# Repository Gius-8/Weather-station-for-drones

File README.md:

## Weather station for drones
The project consists of a kit for drones that includes an electronic device that functions as a meteorological station used for monitoring the values of environmental temperature, of atmospheric pressure and of humidity. The whole device'll work thanks to Arduino/Genuino MKR1000.
The electronic device will have inside a GPS locator so as to know the exact position of the analog readings of the different sensors.
The values acquired will be preserved in a KML files on a microSD and you can view them with Google Earth or Google Maps by simply importing the KML file.
They can be monitored in real time via Wi-Fi hotspot using a Smatphone, Tablet or PC.
In addition to the meteorological data, the device can acquire altitude, geographical coordinates and the speed of the drone in m/s.
The device consumes little power and can be powered by a 3.7V LiPo thanks to the potential of mkr1000 board.
In summary, the device will have the following characteristics:
You will be able to acquire:

- Temperature
- Atmospheric pressure
- Humidity
- Speed
- Altitude drone
- Geographic coordinates

Link tutorial: https://www.hackster.io/gius_8/weather-station-for-drones-1184cd

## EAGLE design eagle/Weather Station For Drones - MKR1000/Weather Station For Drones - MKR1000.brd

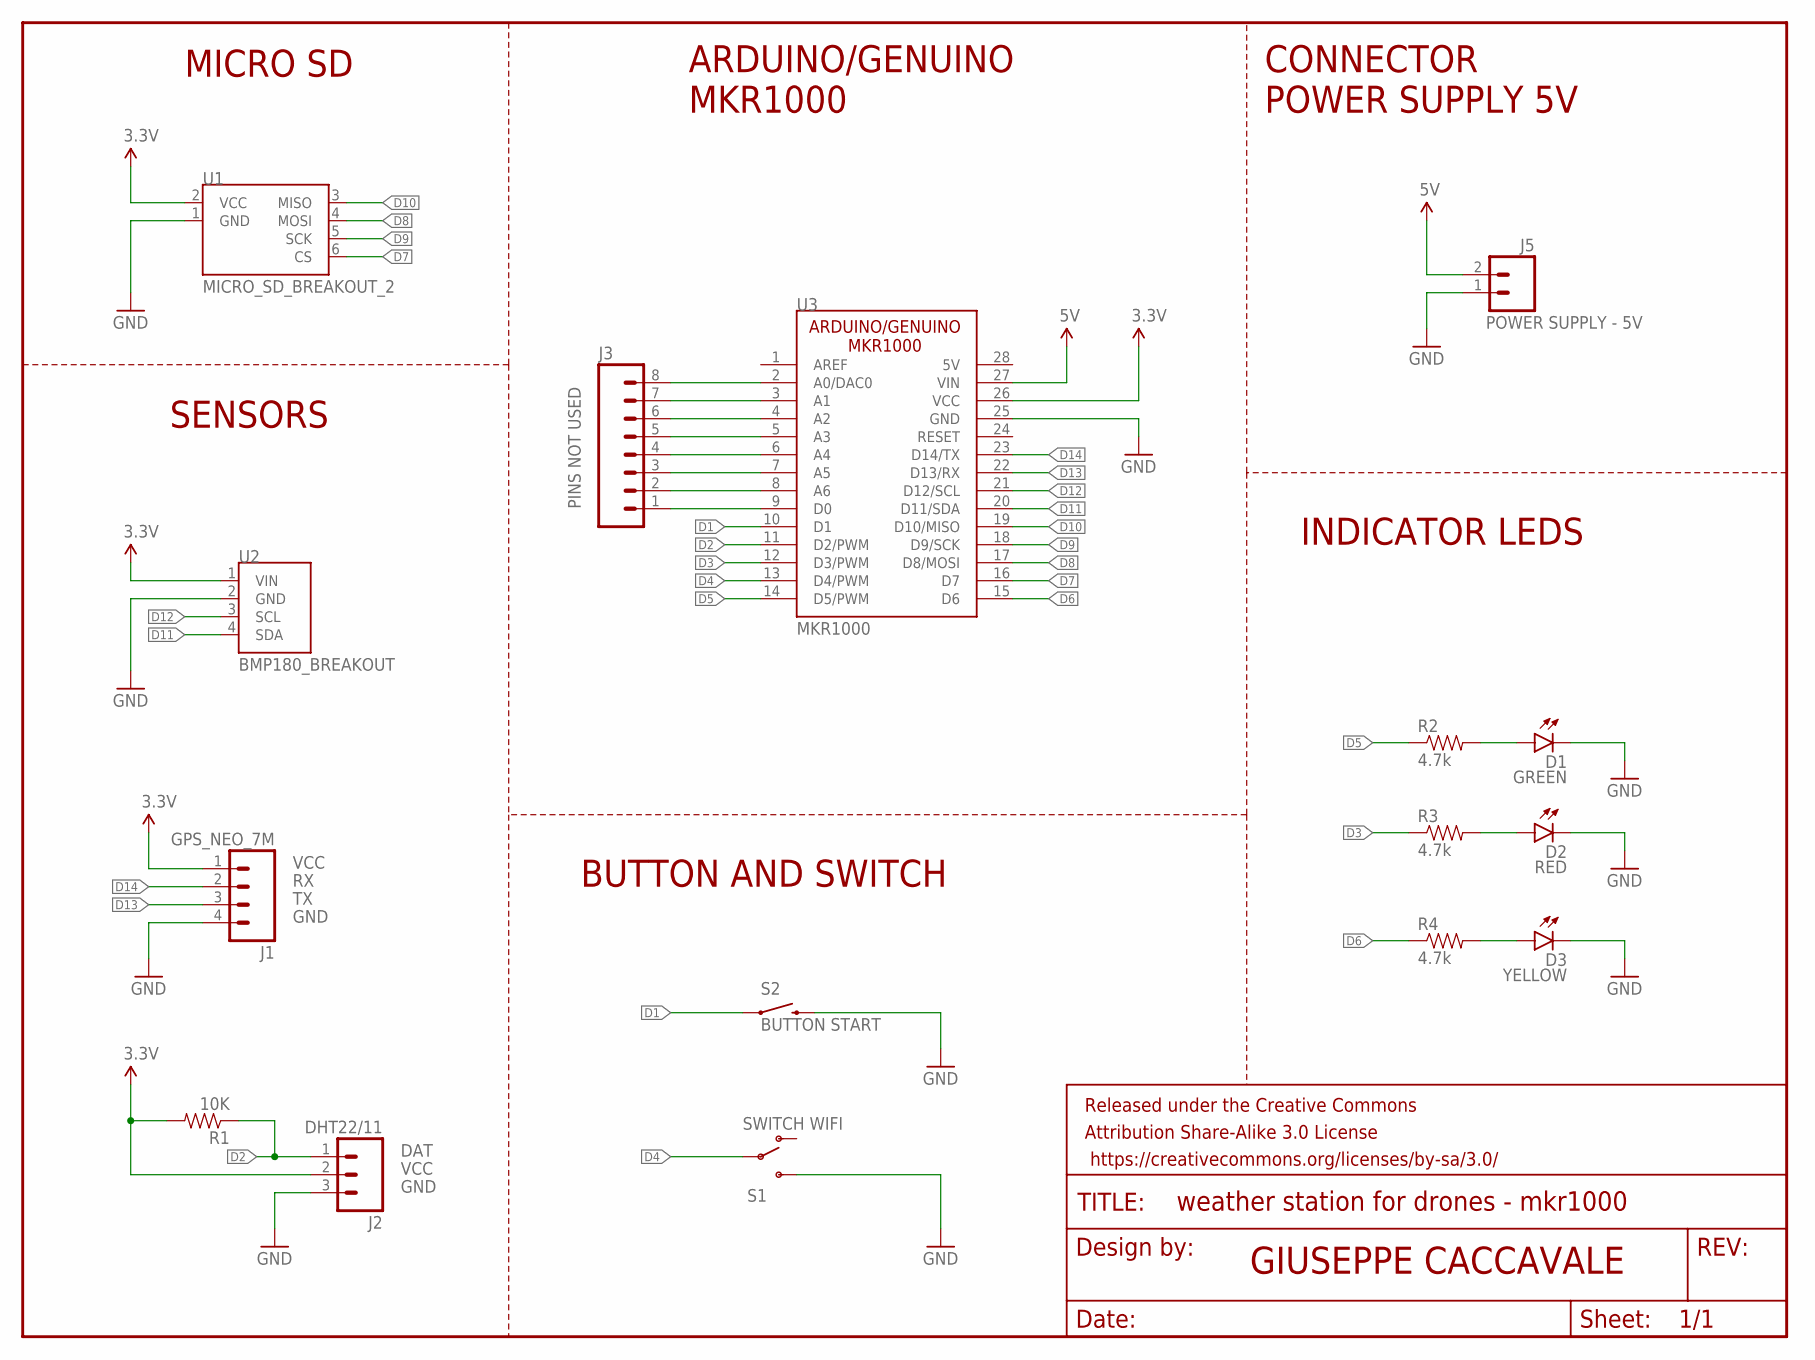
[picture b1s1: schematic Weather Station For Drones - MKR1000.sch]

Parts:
D1: GREEN; LED3MM
D2: RED; LED3MM
D3: YELLOW; LED3MM
FRAME1: FRAME-LETTER; CREATIVE_COMMONS
J1: GPS_NEO_7M; 1X04_LONGPADS
J2: DHT22/11; 1X03_LONGPADS
J3: PINS NOT USED; 1X08_LONGPADS
J5: POWER SUPPLY - 5V; JST-2-PTH
R1: 10K; AXIAL-0.3
R2, R3, R4: 4.7k; AXIAL-0.3
S1: SWITCH WIFI; SWITCH-SPDT_KIT
S2: BUTTON START; TACTILE-PTH
U1: MICRO_SD_BREAKOUT_2; MICRO_SD_ONLY_PIN
U2: BMP180_BREAKOUT
U3: MKR1000

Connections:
3.3V: J1.1, J2.2, R1.P$2 (2), U1.2 (VCC), U2.1 (VIN), U3.26 (VCC)
5V: J5.2, U3.27 (VIN)
D1: S2.1, S2.2 (1), U3.10 (D1)
D2: J2.1, R1.P$1 (1), U3.11 (D2/PWM)
D3: R3.P$1 (1), U3.12 (D3/PWM)
D4: S1.2, U3.13 (D4/PWM)
D5: R2.P$1 (1), U3.14 (D5/PWM)
D6: R4.P$1 (1), U3.15 (D6)
D7: U1.6 (CS), U3.16 (D7)
D8: U1.4 (MOSI), U3.17 (D8/MOSI)
D9: U1.5 (SCK), U3.18 (D9/SCK)
D10: U1.3 (MISO), U3.19 (D10/MISO)
D11: U2.4 (SDA), U3.20 (D11/SDA)
D12: U2.3 (SCL), U3.21 (D12/SCL)
D13: J1.3, U3.22 (D13/RX)
D14: J1.2, U3.23 (D14/TX)
GND: D1.K (C), D2.K (C), D3.K (C), J1.4, J2.3, J5.1, S1.3 (S), S2.3 (2), S2.4 (2), U1.1 (GND), U2.2 (GND), U3.25 (GND)
unnamed: D1.A, R2.P$2 (2)
unnamed: D2.A, R3.P$2 (2)
unnamed: J3.1, U3.9 (D0)
unnamed: J3.2, U3.8 (A6)
unnamed: J3.3, U3.7 (A5)
unnamed: J3.4, U3.6 (A4)
unnamed: J3.5, U3.5 (A3)
unnamed: J3.6, U3.4 (A2)
unnamed: J3.7, U3.3 (A1)
unnamed: J3.8, U3.2 (A0/DAC0)
unnamed: D3.A, R4.P$2 (2)

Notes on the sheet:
GND
VCC
DAT
GIUSEPPE CACCAVALE
SENSORS
CONNECTOR POWER SUPPLY 5V
INDICATOR LEDS
BUTTON AND SWITCH
ARDUINO/GENUINO MKR1000
MICRO SD

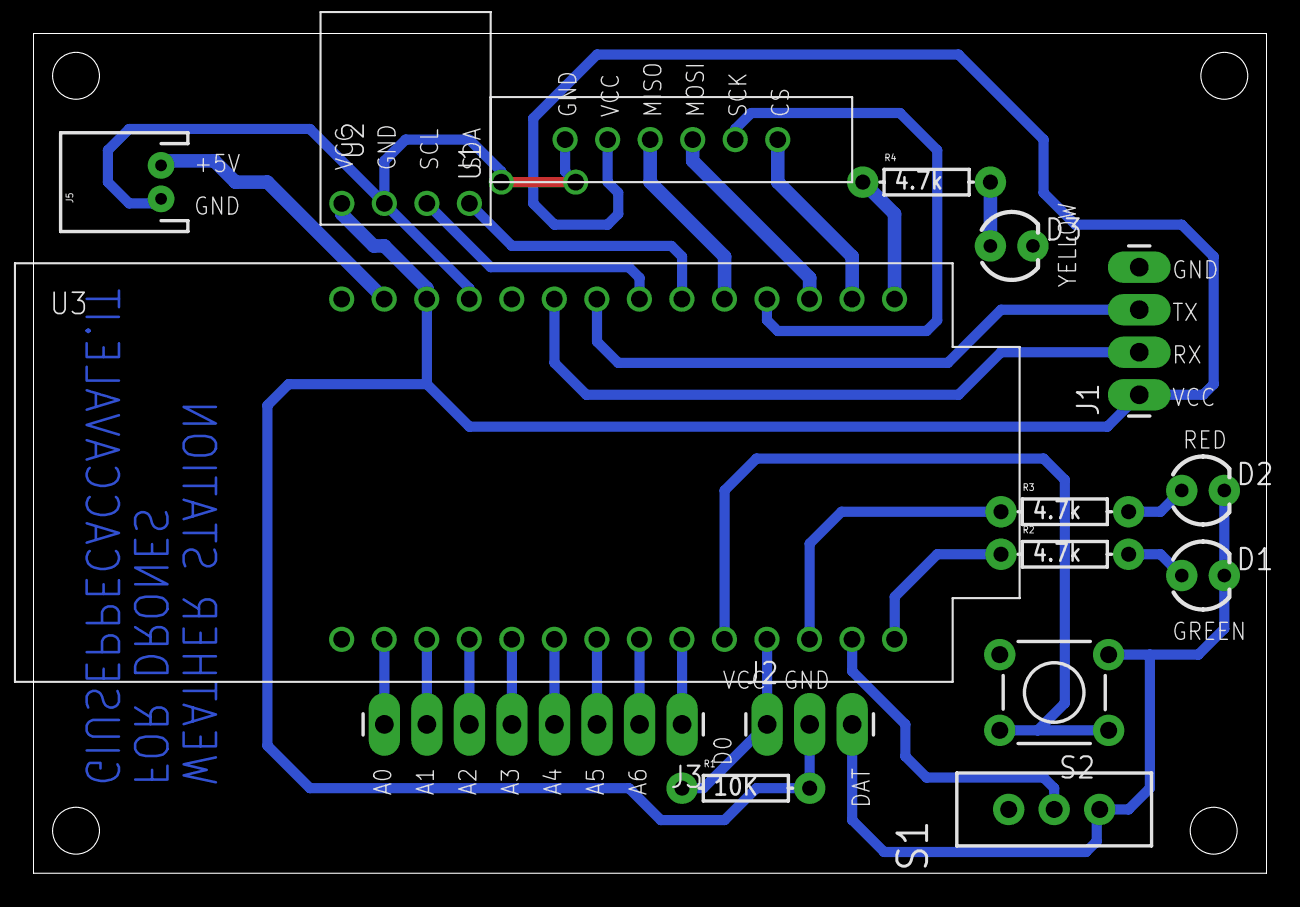
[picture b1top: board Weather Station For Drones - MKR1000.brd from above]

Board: 2 copper layers, 73.6 x 50.2 mm, 17 parts (0 on the bottom side), 28 nets.

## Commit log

2016-03-28 :confetti_ball: Added .gitattributes
2016-03-29 Sketch for Arduino
2016-03-29 readme
2016-03-29 Schematic
2016-03-29 eagle

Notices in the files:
parts and their libraries:
SparkFun-LED: Licensing: Creative Commons ShareAlike 4.0 International - https://creativecommons.org/licenses/by-sa/4.0
SparkFun-Retired: Released under the Creative Commons Attribution Share-Alike 3.0 License
SparkFun-Retired: https://creativecommons.org/licenses/by-sa/3.0
